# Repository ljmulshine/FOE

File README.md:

# FOE
A collection of embedded design projects carried out in the course, the Frustration of Electronics (FOE), a supervised reading and research course I took during the Spring of my sophomore year. These projects have been added to github after completion of the course to showcase my work. 

## Adjustable Power Supply

This project was the first of three embedded design projects I helped lead in ES91r, the Frustration of Electronics. I worked with two others to design a power supply device, originally intended for use by students in Harvard’s introductory electrical engineering course to power their circuits without the need for a benchtop power supply. I lead my team through the brunt of each major design phase, keeping us on track despite simultaneously pipelining other design projects, short turnarounds between project deadlines, and scheduling difficulties among my teammates. After multiple design iterations, we achieved a fully functional, battery powered, adjustable power supply with overvoltage and overcurrent protection, a dynamic range of 1.5V-10V, and the capacity to source or sink current upwards of 500mA. I am currently iterating upon this preliminary design in order to improve upon the device’s absolute maximum ratings and ergonomics. 

## Instrumentation Device

In the second of three embedded circuit design projects for the course, ES91r, I worked with three others to design a high-precision instrumentation device to interface with a load-cell. Precision was a critical consideration throughout the process; consequently, important design considerations were made to ensure signal integrity: utilizing differential signals and an instrumentation amplifier to combat noise, designing an anti-aliasing filter with appropriate pass and stopband frequencies, ensuring a sufficiently high analog-to-digital conversion rate to allow capture of high-speed events, and making layout design decisions that reduced the effect of digital transients and EMI on the analog signal during its travel to the digital realm. We were able to design hardware to allow us to process our signal digitally and save it to a microSD card; however, we were unable to implement the necessary code for this attribute due to time constraints at the end of the semester. In particular, I left this project with a strong understanding of analog-to-digital conversion, and high-precision analog circuit design. 

## Wireless Charging Station

My team and I designed a Wireless Charging Station meant to interface directly with a small remote-control car. While we were unable to produce a physical prototype, iterating completely through an intense design process - creating our own project specifications, conducting research on wireless power transfer, designing the final circuit and PCB, etc. - on a tight time schedule, not only increased my knowledge of power systems, but also proved to be an excellent project experience, pushing me to make intelligent design decisions under pressure.

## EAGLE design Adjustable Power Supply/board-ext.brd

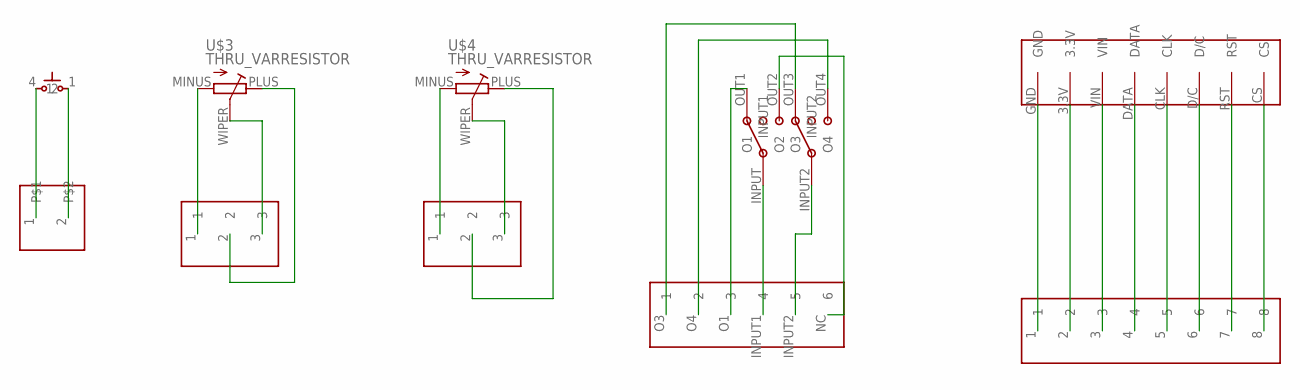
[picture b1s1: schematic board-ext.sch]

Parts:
U$1: 1X02
U$2: BUTTON_THRU; PUSHBTN
U$3, U$4: THRU_VARRESISTOR; POT
U$5, U$6: 1X03
U$7: SWITCH_THRU; DPDT
U$8: 1X06; SWITCHHEAD
U$9: OLED_THRU
U$10: 1X08

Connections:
unnamed: U$1.1, U$2.4 (2)
unnamed: U$1.2, U$2.1
unnamed: U$4.PLUS, U$6.2
unnamed: U$4.MINUS, U$6.1
unnamed: U$4.WIPER, U$6.3
unnamed: U$3.WIPER, U$5.3
unnamed: U$3.PLUS, U$5.2
unnamed: U$3.MINUS, U$5.1
unnamed: U$7.INPUT (INPUT1), U$8.INPUT1 (4)
unnamed: U$7.INPUT2, U$8.INPUT2 (5)
unnamed: U$7.OUT2 (O2), U$8.NC (6)
unnamed: U$7.OUT1 (O1), U$8.O1 (3)
unnamed: U$7.OUT3 (O3), U$8.O3 (1)
unnamed: U$7.OUT4 (O4), U$8.O4 (2)
unnamed: U$9.GND, U$10.1
unnamed: U$9.3.3V, U$10.2
unnamed: U$9.VIN, U$10.3
unnamed: U$9.DATA, U$10.4
unnamed: U$9.CLK, U$10.5
unnamed: U$9.D/C, U$10.6
unnamed: U$9.RST, U$10.7
unnamed: U$9.CS, U$10.8

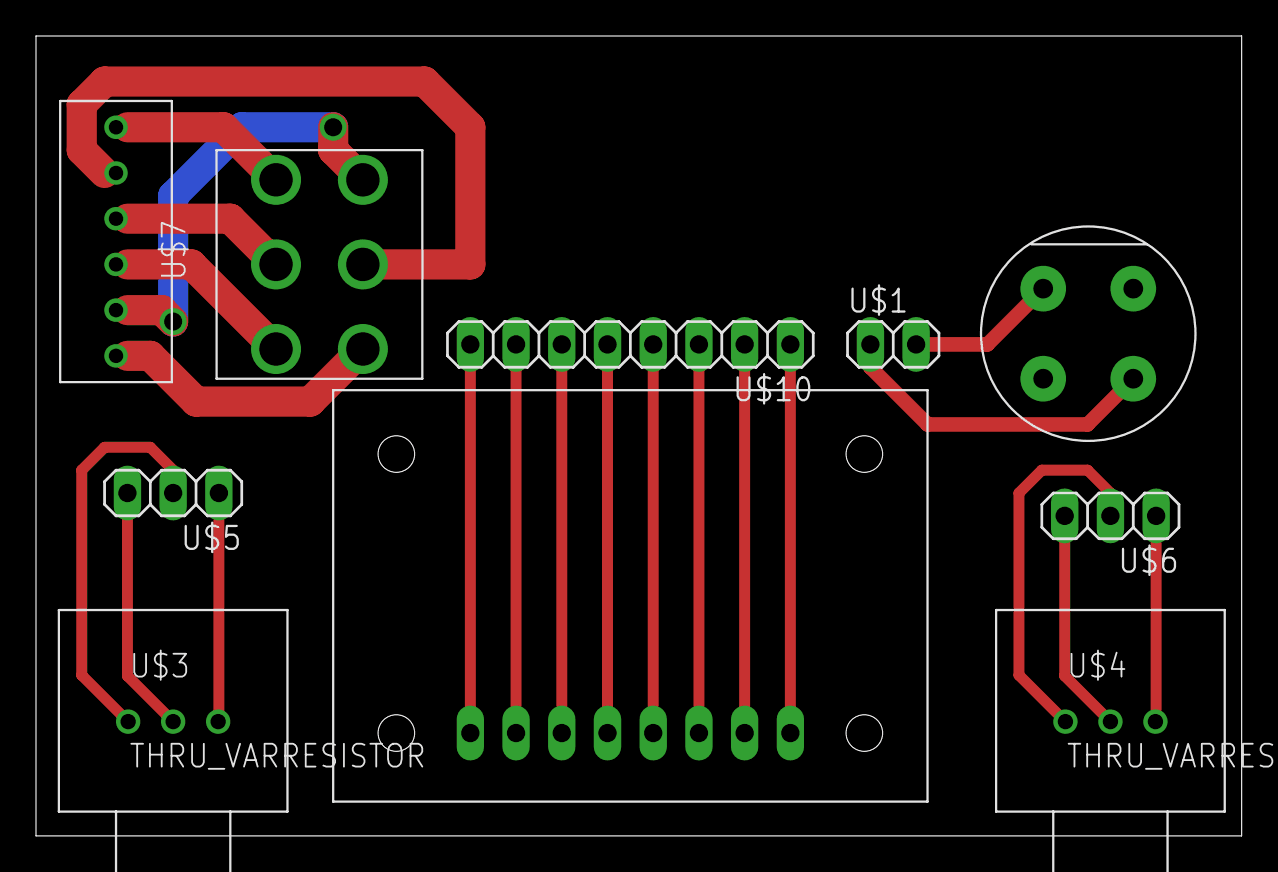
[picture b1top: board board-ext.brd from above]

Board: 2 copper layers, 67.0 x 44.4 mm, 10 parts (0 on the bottom side), 22 nets.

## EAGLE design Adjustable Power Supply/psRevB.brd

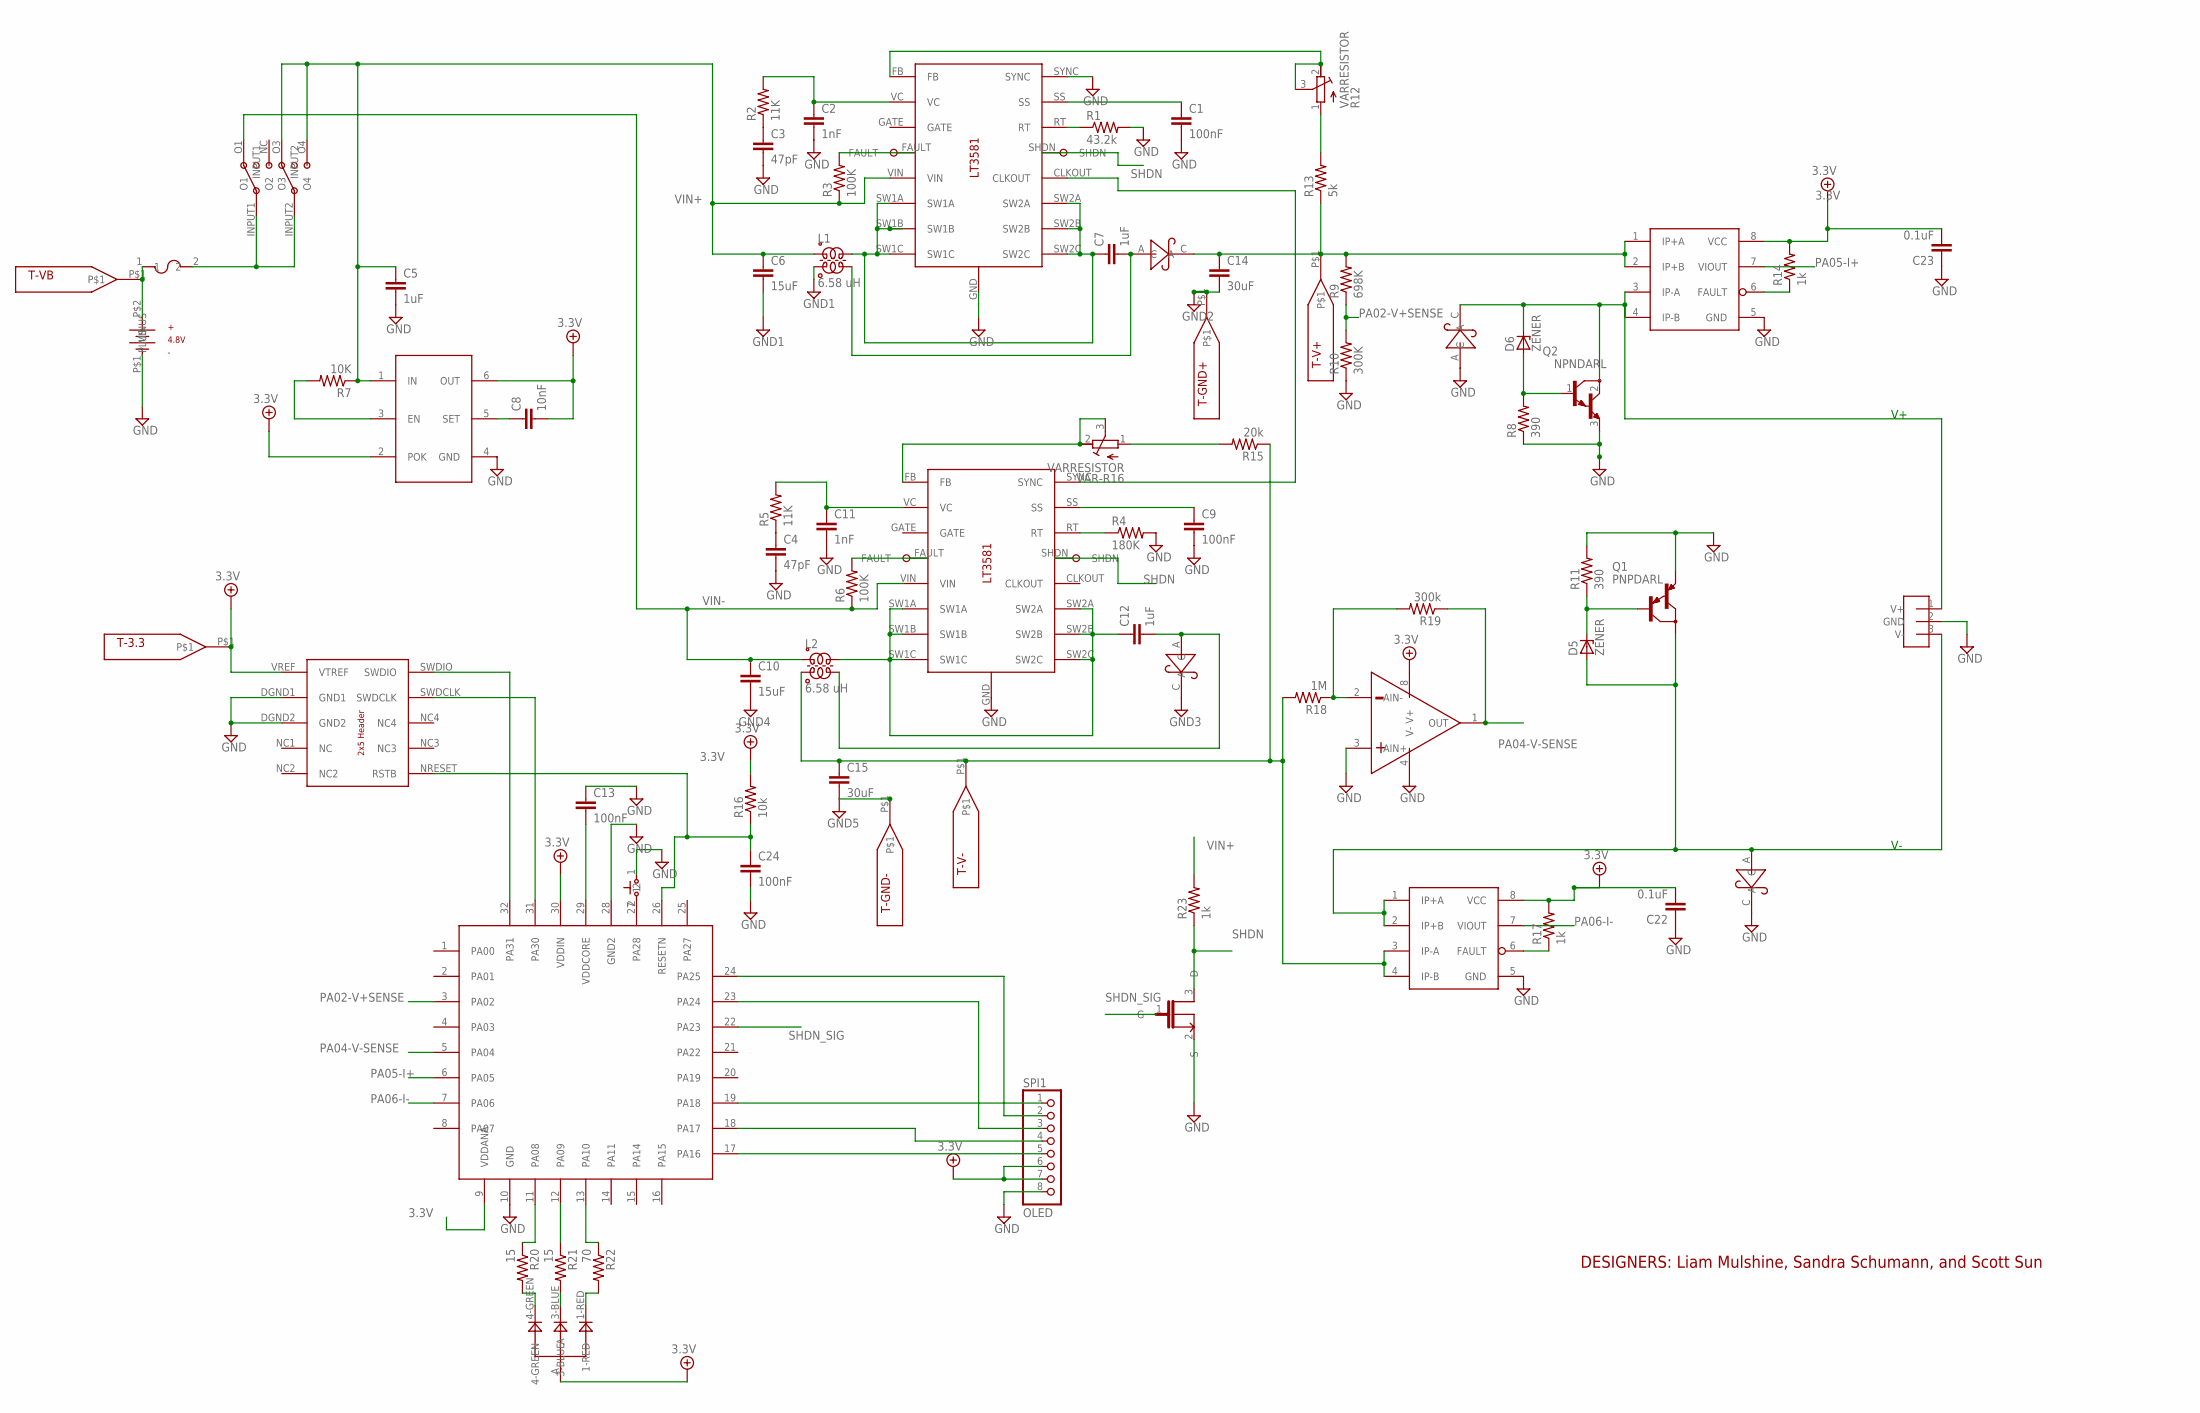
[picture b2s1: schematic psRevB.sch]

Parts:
BT1: BATTERY; POWERHEAD
C1: 100nF; C0603K
C2: 1nF; C0603K
C3: 47pF; C0603K
C4: 47pF; C0805
C5, C7, C12: 1uF; C0805
C6, C10: 15uF; C0805
C8: 10nF; C0805
C9, C13, C24: 100nF; C0805
C11: 1nF; C0805
C14, C15: 30uF; C1206K
C22, C23: 0.1uF; C0805
D1, D2, D3, D4: SCHTKYDIODE
D5, D6: ZENER
DBG1: DEBUGHEAD
F1: FUSE
L1: 6.58 uH; COUPLED_INDUCTOR@1
L2: 6.58 uH; COUPLED_INDUCTOR
Q1: PNPDARL; DPAKTO252
Q2: NPNDARL; DPAKTO252
R1: 43.2k; R0603
R2, R5: 11K; R0603
R3, R6: 100K; R0603
R4: 180K; R0603
R7: 10K; R0603
R8, R11: 390; R0603
R9: 698K; R0603
R10: 300K; R0603
R12: VARRESISTOR; 1X03
R13: 5k; R0603
R14, R17, R23: 1k; R0603
R15: 20k; R0603
R16: 10k; R0603
R18: 1M; R0603
R19: 300k; R0603
R20, R21: 15; R0603
R22: 70; R0603
S1: DPDT; SWITCHHEAD
S2: PUSHBTN; 1X02
SPI1: OLED; 1X08
T-3.3: TEST_POINT
T-GND+: TEST_POINT
T-GND-: TEST_POINT
T-V+: TEST_POINT
T-V-: TEST_POINT
T-VB: TEST_POINT
U1, U7: LT3581
U2: SAMD21E; TQFP32-08
U3: AS1363; SOT23-6
U4: VOUT; 1X03
U5, U6: ACS711; SOIC8
U8: RGBLED
U9: LMC6482; SOIC8
U$1: NMOS; SOT23-3
VAR-R16: VARRESISTOR; 1X03

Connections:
3.3V: C8.2, C22.2, C23.2, DBG1.VREF (VTREF), R14.2, R16.2, R17.2, SPI1.6 (VIN1), SPI1.7 (VIN2), T-3.3.P$1, U2.9 (VDDANA), U2.30 (VDDIN), U3.2 (POK), U3.6 (OUT), U5.8 (VCC), U6.8 (VCC), U8.A, U9.8 (V+)
GND: BT1.P$1 (MINUS), C1.2, C2.2, C3.2, C4.2, C5.2, C6.2, C9.2, C10.2, C11.2, C13.1, C14.2, C15.2, C22.1, C23.1, C24.2, D1.C, D2.C, D3.A, DBG1.DGND1 (GND1), DBG1.DGND2 (GND2), L1.L2A (2), Q1.3 (E), Q2.3 (E), R1.2, R4.2, R8.1, R10.1, R11.2, S2.1, SPI1.8 (GND), T-GND+.P$1, T-GND-.P$1, U1.GND, U1.SYNC, U2.10 (GND), U2.28 (GND2), U3.4 (GND), U4.2 (GND), U5.5 (GND), U6.5 (GND), U7.GND, U9.3 (AIN+), U9.4 (V-), U$1.2 (S)
unnamed: R1.1, U1.RT
unnamed: C1.1, U1.SS
unnamed: C3.1, R2.1
unnamed: C2.1, R2.2, U1.VC
unnamed: R4.1, U7.RT
unnamed: C9.1, U7.SS
unnamed: C4.1, R5.1
unnamed: C11.1, R5.2, U7.VC
unnamed: S2.2, U2.27 (PA28)
unnamed: D3.C, D6.C, Q2.2 (C), U4.1 (V+), U5.3 (IP-A), U5.4 (IP-B)
unnamed: C12.2, D1.A, L2.L2B (4)
unnamed: R17.1, U6.6 (FAULT)
unnamed: C8.1, U3.5 (SET)
unnamed: U7.FB, VAR-R16.2 (PLUS), VAR-R16.3 (WIPER)
unnamed: R12.2 (PLUS), R12.3 (WIPER), U1.FB
unnamed: R7.2, U3.3 (EN)
unnamed: C24.1, DBG1.NRESET (RSTB), R16.1, U2.26 (RESETN)
unnamed: D6.A, Q2.1 (B), R8.2
unnamed: BT1.P$2 (PLUS), F1.1, T-VB.P$1
unnamed: C7.1, L1.L1B (3), U1.SW1A, U1.SW1B, U1.SW1C, U1.SW2A, U1.SW2B, U1.SW2C
unnamed: C12.1, L2.L1B (3), U7.SW1A, U7.SW1B, U7.SW1C, U7.SW2A, U7.SW2B, U7.SW2C
unnamed: R15.2, VAR-R16.1 (MINUS)
unnamed: C7.2, D4.A, L1.L2B (4)
unnamed: D5.C, Q1.1 (B), R11.1
unnamed: C15.1, L2.L2A (2), R15.1, R18.2, T-V-.P$1, U6.3 (IP-A), U6.4 (IP-B)
unnamed: C14.1, D4.C, R9.2, R13.1, T-V+.P$1, U5.1 (IP+A), U5.2 (IP+B)
unnamed: R12.1 (MINUS), R13.2
unnamed: R18.1, R19.2, U9.2 (AIN-)
unnamed: R14.1, U5.6 (FAULT)
unnamed: R20.2, U8.4-GREEN
unnamed: R21.2, U8.3-BLUE
unnamed: R22.2, U8.1-RED
unnamed: D2.A, D5.A, Q1.2 (C), U4.3 (V-), U6.1 (IP+A), U6.2 (IP+B)
unnamed: R20.1, U2.11 (PA08)
unnamed: R21.1, U2.12 (PA09)
unnamed: R22.1, U2.13 (PA10)
unnamed: C13.2, U2.29 (VDDCORE)
unnamed: DBG1.SWDIO, U2.32 (PA31)
unnamed: DBG1.SWDCLK, U2.31 (PA30)
unnamed: SPI1.1 (CS), U2.19 (PA18)
unnamed: SPI1.2 (RST), U2.24 (PA25)
unnamed: SPI1.3 (D/C), U2.23 (PA24)
unnamed: SPI1.5 (DATA), U2.17 (PA16)
unnamed: SPI1.4 (CLK), U2.18 (PA17)
unnamed: F1.2, S1.INPUT1, S1.INPUT2
PA02-V+SENSE: R9.1, R10.2, U2.3 (PA02)
PA04-V-SENSE: R19.1, U2.5 (PA04), U9.1 (OUT)
PA05-I+: U2.6 (PA05), U5.7 (VIOUT)
PA06-I-: U2.7 (PA06), U6.7 (VIOUT)
PA11-FAULT1: R3.2, U1.FAULT
PA19-FAULT2: R6.2, U7.FAULT
SHDN: R23.1, U1.SHDN, U7.SHDN, U$1.3 (D)
SHDN_SIG: U2.22 (PA23), U$1.1 (G)
SYNC: U1.CLKOUT, U7.SYNC
VIN+: C5.1, C6.1, L1.L1A (1), R3.1, R7.1, R23.2, S1.O3, S1.O4, U1.VIN, U3.1 (IN)
VIN-: C10.1, L2.L1A (1), R6.1, S1.O1, U7.VIN

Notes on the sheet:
DESIGNERS: Liam Mulshine, Sandra Schumann, and Scott Sun

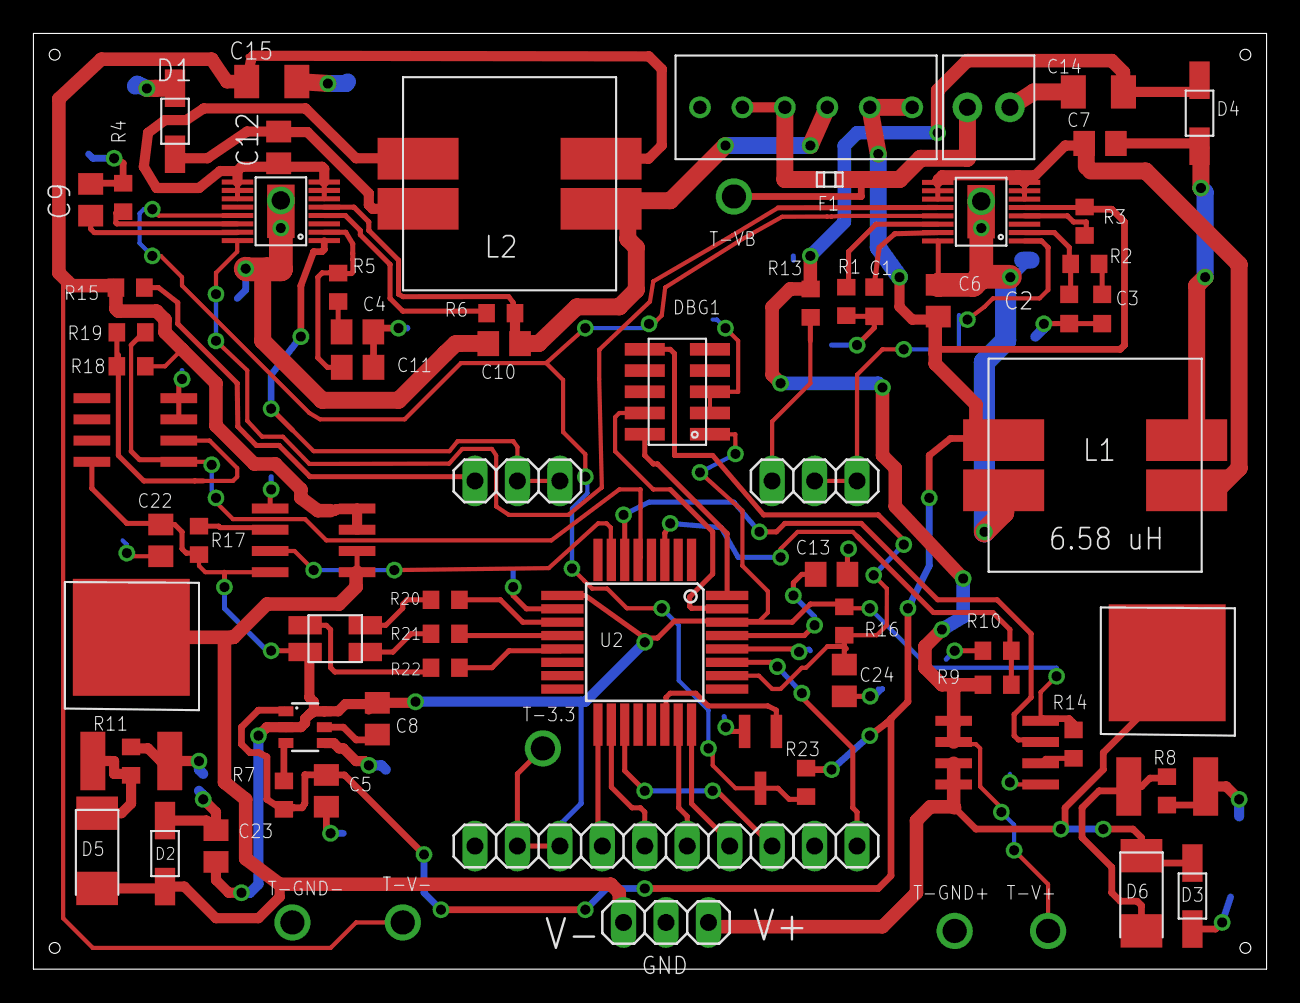
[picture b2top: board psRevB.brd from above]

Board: 2 copper layers, 73.8 x 56.0 mm, 74 parts (0 on the bottom side), 58 nets.

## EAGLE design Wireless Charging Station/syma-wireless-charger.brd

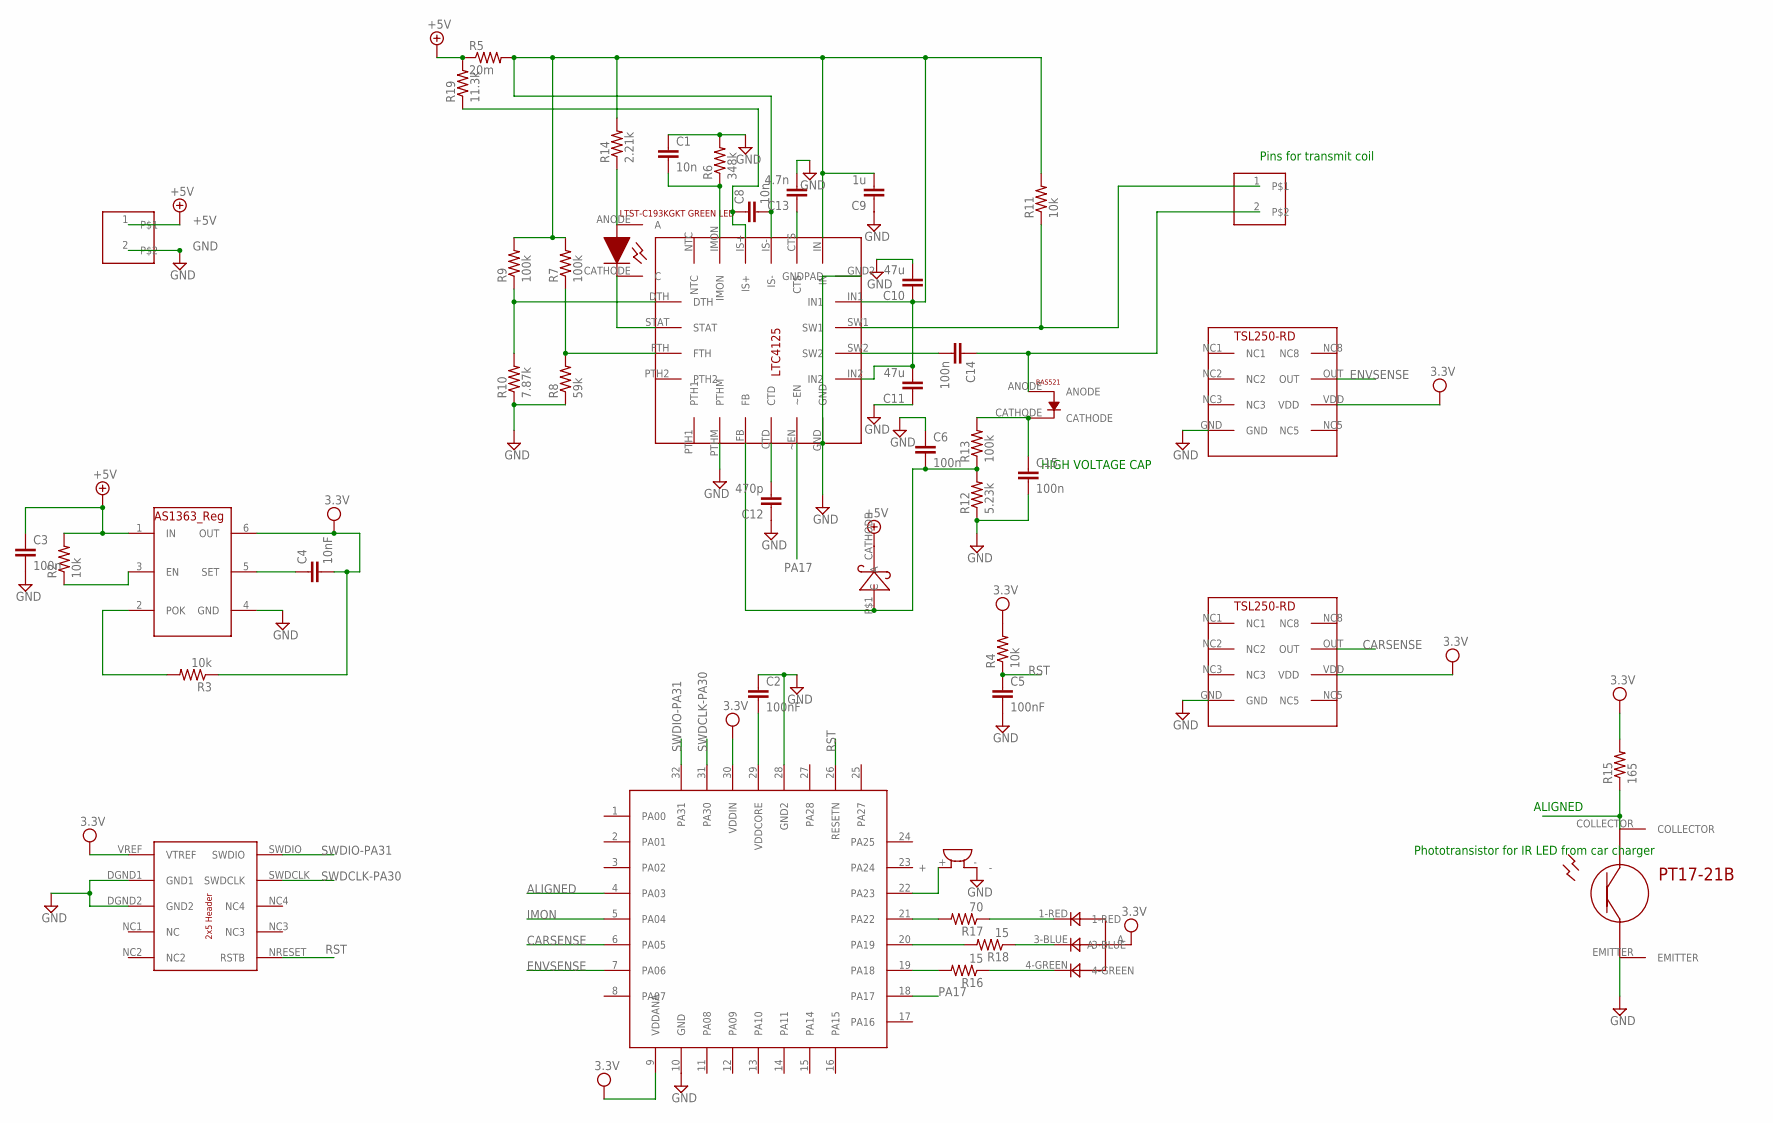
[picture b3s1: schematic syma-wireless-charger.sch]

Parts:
C1, C8: 10n; C0805
C2, C5: 100nF; C0805K
C3: 100n; C0805K
C4: 10nF; C0805K
C6: 100n; C0805
C9: 1u; C0805
C10, C11: 47u; C0805
C12: 470p; C0805
C13: 4.7n; C0805
C14: 100n; C1206
C15: 100n; C0603
DBG1: DEBUGHEAD
R2, R3, R4, R11: 10k; R0805
R5: 20m; R0805
R6: 348k; R0805
R7, R9, R13: 100k; R0805
R8: 59k; R0805
R10: 7.87k; R0805
R12: 5.23k; R0805
R14: 2.21k; R0805
R15: 165; R0805
R16, R18: 15; R0805
R17: 70; R0805
R19: 11.3k; R0805
U1: SAMD21E; TQFP32-08
U2: 3.3V_AS1363; SOT23-6
U$1: LTC4125; LTC1945-QFN
U$2: BAS521; BAS521-V-DIODE
U$3, U$11: 1X02
U$4: RGBLED
U$5: BUZZER
U$6, U$7: TSL250-RD
U$8: SCHTKYDIODE-523; SOD-523
U$9: LTST-C193KGKT_GREEN-LED
U$10: PT17-21B_PHOTOTRANSISTOR

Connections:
+5V: C3.1, R2.2, R5.1, R19.2, U2.1 (IN), U$3.1, U$8.CATHODE (C)
ALIGNED: R15.1, U1.4 (PA03), U$10.COLLECTOR
CARSENSE: U1.6 (PA05), U$6.OUT
ENVSENSE: U1.7 (PA06), U$7.OUT
GND: C1.1, C2.1, C3.2, C5.2, C6.1, C9.1, C10.2, C11.1, C12.1, C13.2, C15.2, DBG1.DGND1 (GND1), DBG1.DGND2 (GND2), R6.2, R8.1, R10.1, R12.1, U1.10 (GND), U1.28 (GND2), U2.4 (GND), U$1.GND, U$1.GND2 (GNDPAD), U$1.PTHM, U$3.2, U$5.-, U$6.GND, U$7.GND, U$10.EMITTER
IMON: C1.2, R6.1, U1.5 (PA04), U$1.IMON
unnamed: C2.2, U1.29 (VDDCORE)
unnamed: R3.2, U2.2 (POK)
unnamed: R2.1, U2.3 (EN)
unnamed: R9.1, R10.2, U$1.DTH
unnamed: C4.1, U2.5 (SET)
unnamed: R7.1, R8.2, U$1.FTH
unnamed: R11.1, U$1.SW1, U$11.1
unnamed: C6.2, R12.2, R13.1, U$1.FB, U$8.P$1 (A)
unnamed: C15.1, R13.2, U$2.CATHODE
unnamed: R14.1, U$9.ANODE (A)
unnamed: C14.1, U$2.ANODE, U$11.2
unnamed: R17.2, U1.21 (PA22)
unnamed: R18.2, U1.20 (PA19)
unnamed: R16.2, U1.19 (PA18)
unnamed: R16.1, U$4.4-GREEN
unnamed: R18.1, U$4.3-BLUE
unnamed: R17.1, U$4.1-RED
unnamed: U1.22 (PA23), U$5.+
unnamed: C8.2, C9.2, C10.1, C11.2, R5.2, R7.2, R9.2, R11.2, R14.2, U$1.IN, U$1.IN1, U$1.IN2, U$1.IS-
unnamed: C8.1, R19.1, U$1.IS+
unnamed: C14.2, U$1.SW2
unnamed: U$1.STAT, U$9.CATHODE (C)
unnamed: C12.2, U$1.CTD
unnamed: C13.1, U$1.CTS
PA17: U1.18 (PA17), U$1.~EN
RST: C5.1, DBG1.NRESET (RSTB), R4.1, U1.26 (RESETN)
SWDCLK-PA30: DBG1.SWDCLK, U1.31 (PA30)
SWDIO-PA31: DBG1.SWDIO, U1.32 (PA31)
VDD: C4.2, DBG1.VREF (VTREF), R3.1, R4.2, R15.2, U1.9 (VDDANA), U1.30 (VDDIN), U2.6 (OUT), U$4.A, U$6.VDD, U$7.VDD

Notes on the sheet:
Phototransistor for IR LED from car charger
Pins for transmit coil
HIGH VOLTAGE CAP
ALIGNED

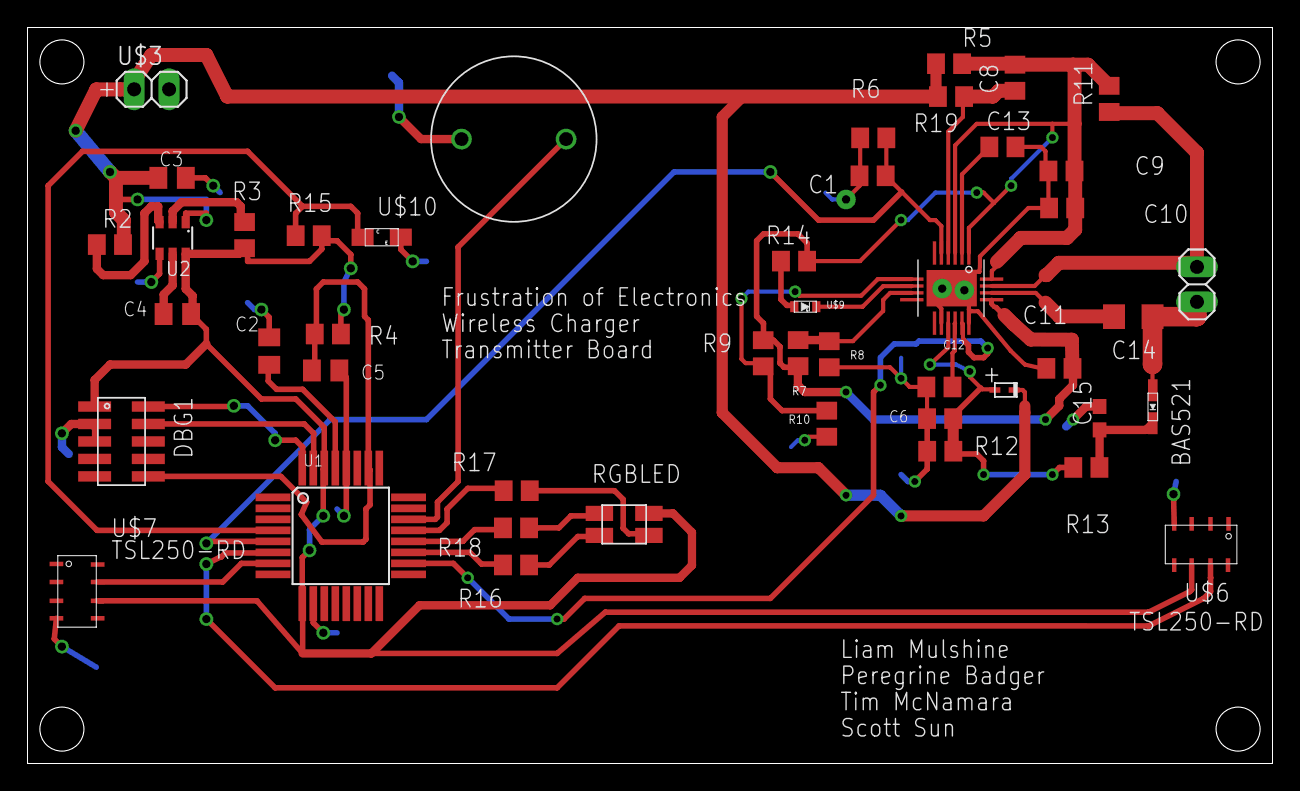
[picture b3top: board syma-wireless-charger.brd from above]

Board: 2 copper layers, 90.5 x 53.5 mm, 46 parts (0 on the bottom side), 35 nets.

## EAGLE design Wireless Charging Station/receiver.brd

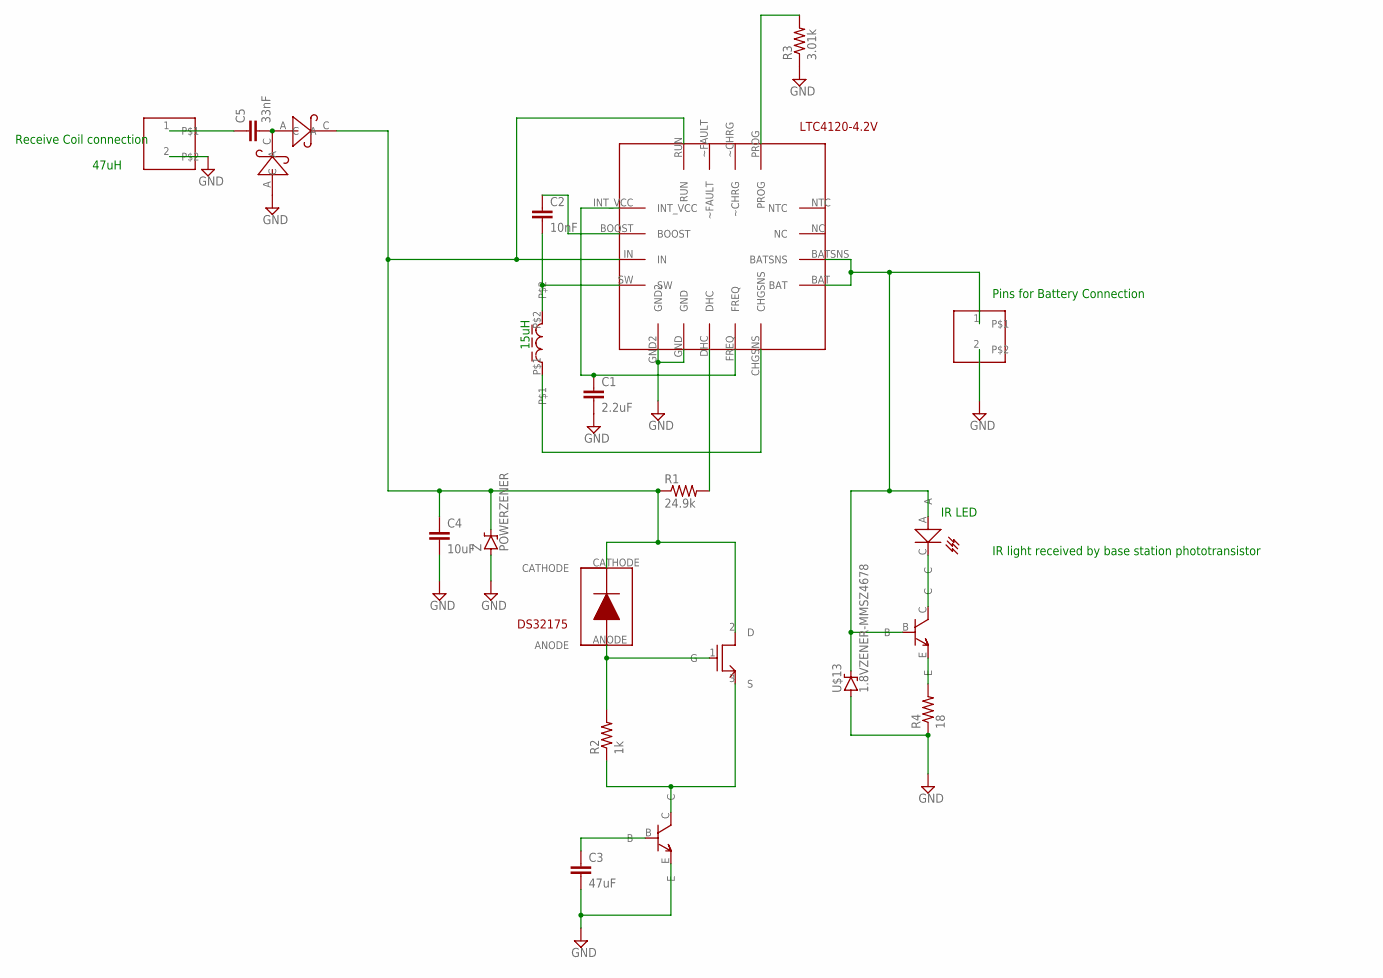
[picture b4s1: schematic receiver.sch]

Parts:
C1: 2.2uF; C0805K
C2: 10nF; C0805K
C3: 47uF; C0805K
C4: 10uF; C0805K
C5: 33nF; C0805K
PS, PS2: SCHTKYPOWER; POWERDI123
R1: 24.9k; R0805
R2: 1k; R0805
R3: 3.01k; R0805
R4: 18; R0805
U$1: LTC4120-4.2V
U$2, U$10: 1X02
U$3: 15UH-INDUCTOR
U$4: BAS521; BAS521-V-DIODE
U$5: M1-RSD140P06; DPAKTO252
U$6, U$14: NPN-MMBT3904; SOT23
U$11: IRLED
U$13: 1.8VZENER-MMSZ4678; SOD-123
Z: POWERZENER; POWERDI123

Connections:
GND: C1.2, C3.2, C4.2, PS2.A, R3.1, R4.1, U$1.GND, U$1.GND2, U$2.2, U$6.E, U$10.2, U$13.A, Z.A
unnamed: C1.1, U$1.FREQ, U$1.INT_VCC
unnamed: U$1.CHGSNS, U$3.P$1
unnamed: C4.1, PS.C, R1.1, U$1.IN, U$1.RUN, U$4.CATHODE, U$5.2 (D), Z.C
unnamed: C2.1, U$1.BOOST
unnamed: C2.2, U$1.SW, U$3.P$2
unnamed: R1.2, U$1.DHC
unnamed: R2.2, U$4.ANODE, U$5.1 (G)
unnamed: R2.1, U$5.3 (S), U$6.C
unnamed: C5.1, U$2.1
unnamed: C5.2, PS.A, PS2.C
unnamed: C3.1, U$6.B
unnamed: R3.2, U$1.PROG
unnamed: U$1.BAT, U$1.BATSNS, U$10.1, U$11.A, U$13.C, U$14.B
unnamed: R4.2, U$14.E
unnamed: U$11.C, U$14.C

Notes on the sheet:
15uH
Pins for Battery Connection
IR LED
IR light received by base station phototransistor
Receive Coil connection
47uH

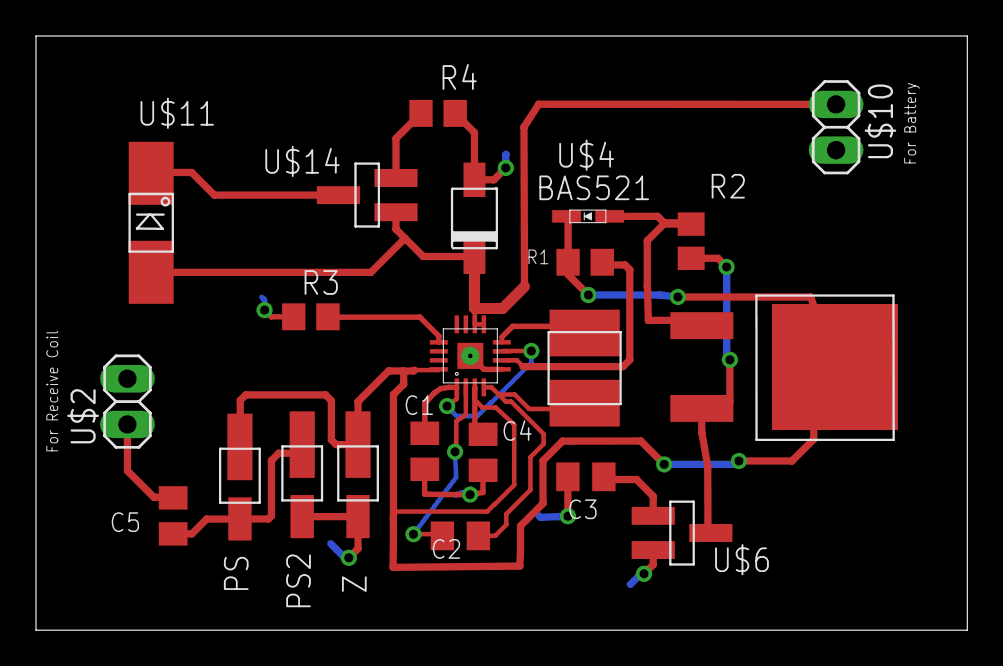
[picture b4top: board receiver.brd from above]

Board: 2 copper layers, 51.7 x 33.0 mm, 22 parts (0 on the bottom side), 16 nets.

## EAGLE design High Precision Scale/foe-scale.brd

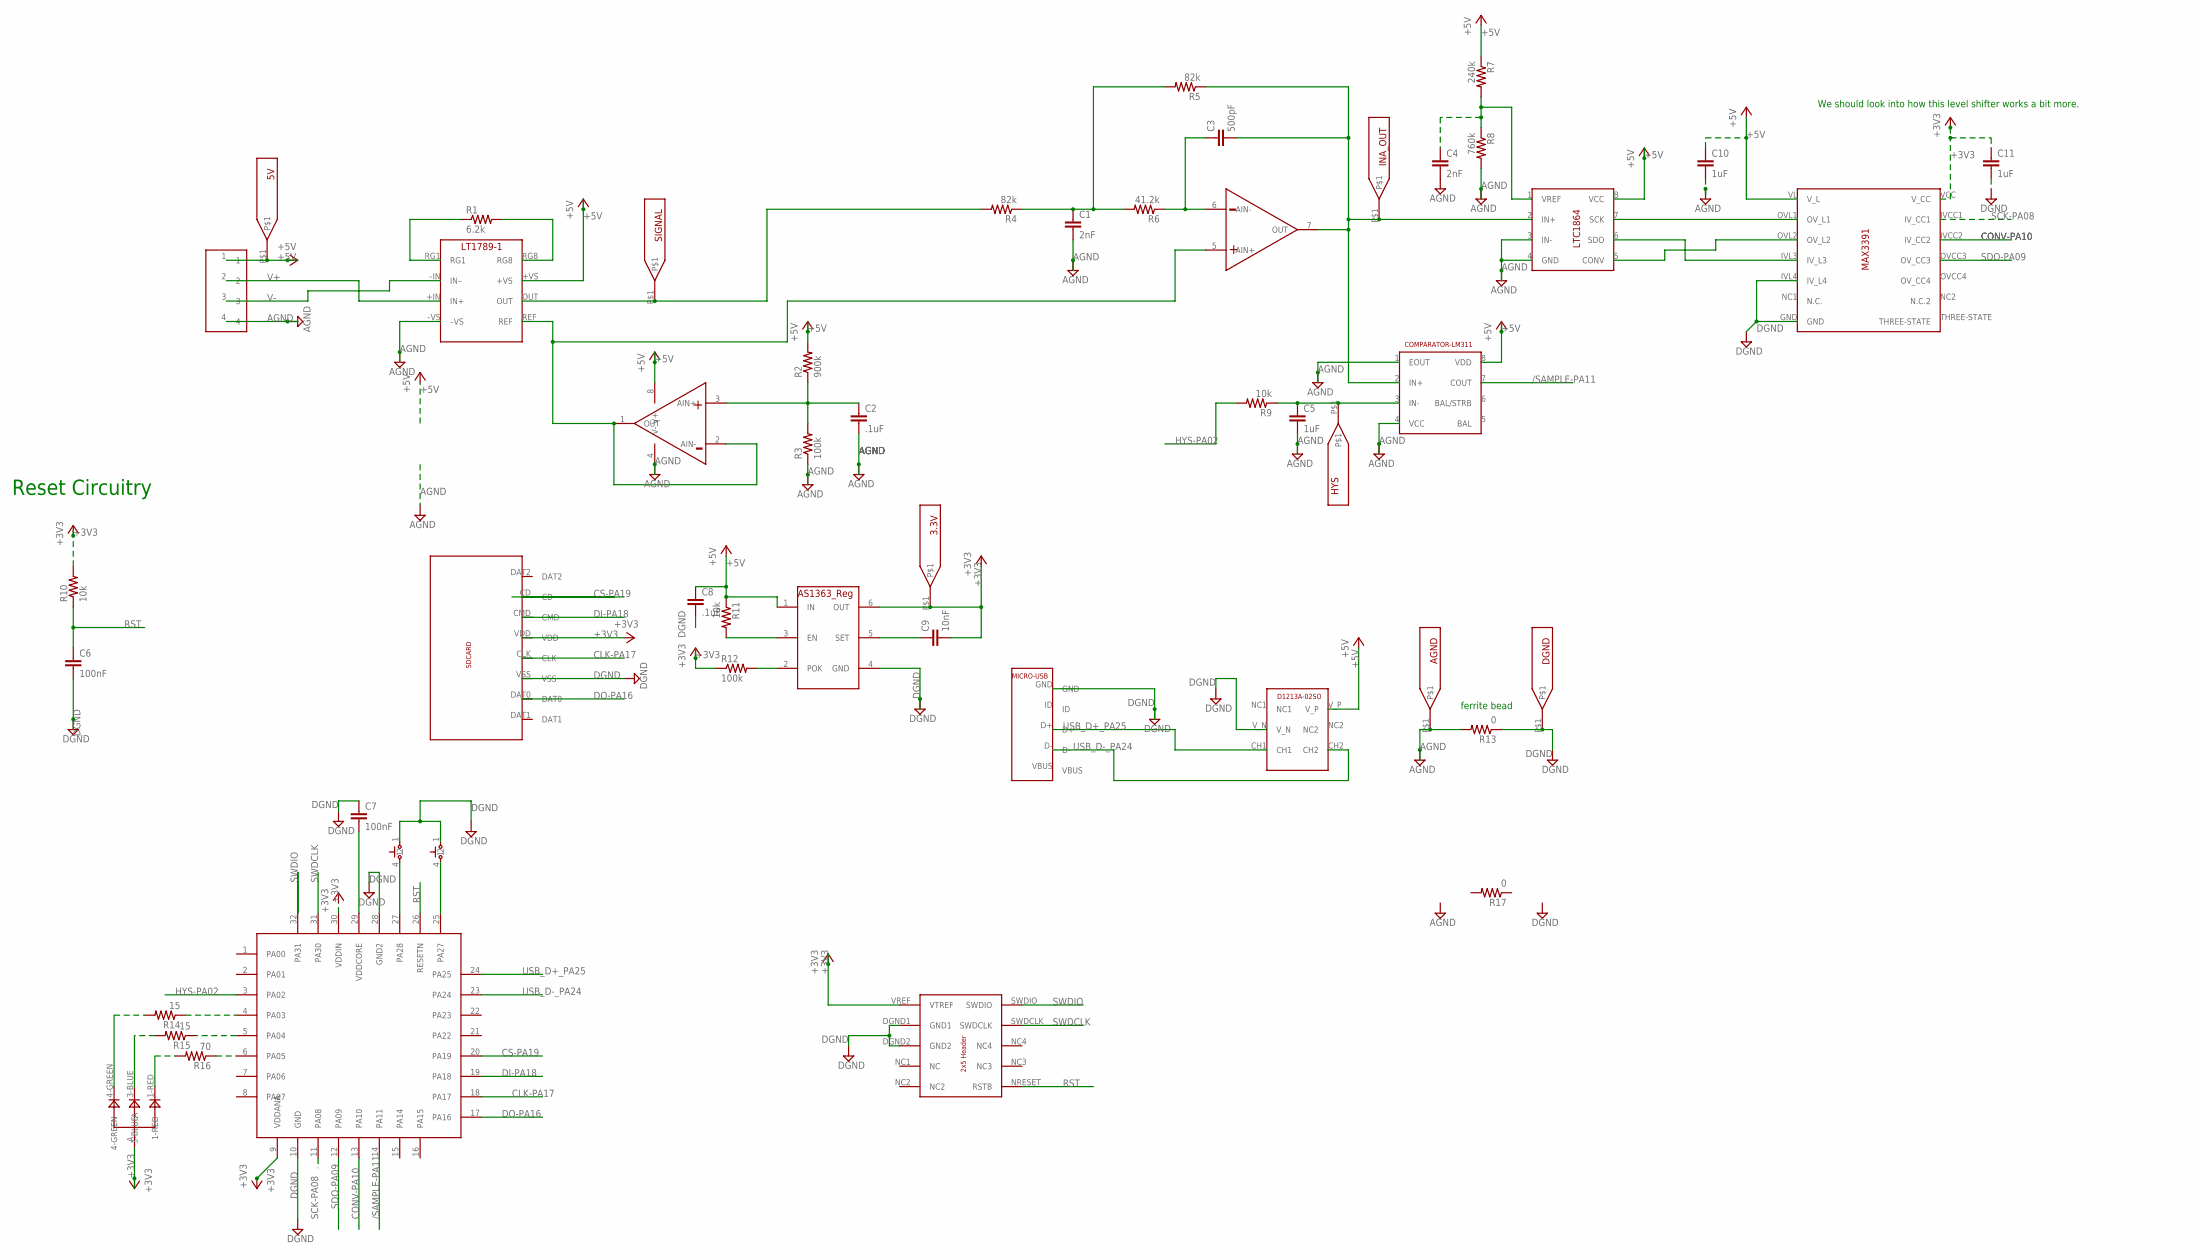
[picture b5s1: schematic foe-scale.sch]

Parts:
3.3V, 5V: TEST_POINT
AGND: TEST_POINT
AS1363: 3.3V_AS1363; SOT23-6
C1, C4: 2nF; C0805K
C2, C8: .1uF; C0805K
C3: 500pF; C0805K
C5, C10, C11: 1uF; C0805K
C6, C7: 100nF; C0805K
C9: 10nF; C0805K
D1: D1213A-DIODE-ARRAY; SOT26-DIODE-ARRAY
DBG1: DEBUGHEAD
DGND: TEST_POINT
HYS: TEST_POINT
INA_OUT: TEST_POINT
R1: 6.2k; R0805
R2: 900k; R0805
R3, R12: 100k; R0805
R4, R5: 82k; R0805
R6: 41.2k; R0805
R7: 240k; R0805
R8: 760k; R0805
R9, R10, R11: 10k; R0805
R13, R17: 0; R0805
R14, R15: 15; R0805
R16: 70; R0805
SIGNAL: TEST_POINT
U1: LM311; SOIC8
U2: SAMD21E; TQFP32-08
U$1: 1X04
U$2: LT1789-1-INSTR-AMP; S8-LT1789-1
U$3: LMC6482; SOIC8
U$6: ADC-LTC1864; SOIC8
U$7: LEVEL-SHIFTER; TSSOP-14
U$8: SDCARD_JACK; MICRO_SDCARD
U$10: RGBLED
U$11, U$12: BUTTON_THRU; PUSHBTN
U$13: MICRO-USB-CONNECTOR

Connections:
+3V3: 3.3V.P$1, AS1363.6 (OUT), C9.2, C11.1, DBG1.VREF (VTREF), R10.2, R12.1, U2.9 (VDDANA), U2.30 (VDDIN), U$7.VCC (V_CC), U$8.VDD, U$10.A
+5V: 5V.P$1, AS1363.1 (IN), C8.1, C10.1, D1.V_P, R2.2, R7.1, R11.1, U1.8 (VDD), U$1.1, U$2.+VS, U$3.8 (V+), U$6.8 (VCC), U$7.VL (V_L)
/SAMPLE-PA11: U1.7 (COUT), U2.14 (PA11)
AGND: AGND.P$1, C1.2, C2.2, C4.2, C5.2, C10.2, R3.1, R8.2, R13.2, U1.1 (EOUT), U1.4 (VCC), U$1.4, U$2.–VS, U$3.4 (V-), U$6.3 (IN-), U$6.4 (GND)
CLK-PA17: U2.18 (PA17), U$8.CLK
CONV-PA10: U2.13 (PA10), U$7.IVCC2 (IV_CC2)
CS-PA19: U2.20 (PA19), U$8.CD
DGND: AS1363.4 (GND), C6.2, C7.1, C8.2, C11.2, D1.V_N, DBG1.DGND1 (GND1), DBG1.DGND2 (GND2), DGND.P$1, R13.1, U2.10 (GND), U2.28 (GND2), U$7.GND, U$7.IVL4 (IV_L4), U$8.VSS, U$11.1, U$12.1, U$13.GND
DI-PA18: U2.19 (PA18), U$8.CMD
DO-PA16: U2.17 (PA16), U$8.DAT0
HYS-PA02: R9.2, U2.3 (PA02)
unnamed: R14.1, U2.4 (PA03)
unnamed: U2.27 (PA28), U$12.4 (2)
unnamed: U2.25 (PA27), U$11.4 (2)
unnamed: R15.1, U2.5 (PA04)
unnamed: R1.1, U$2.RG1
unnamed: R1.2, U$2.RG8
unnamed: R4.2, SIGNAL.P$1, U$2.OUT
unnamed: R16.1, U2.6 (PA05)
unnamed: C2.1, R2.1, R3.2, U$3.3 (AIN+)
unnamed: U$2.REF, U$3.1 (OUT), U$3.2 (AIN-), U$3.5 (AIN+)
unnamed: C1.1, R4.1, R5.2, R6.2
unnamed: C3.2, INA_OUT.P$1, R5.1, U1.2 (IN+), U$3.7 (OUT), U$6.2 (IN+)
unnamed: C3.1, R6.1, U$3.6 (AIN-)
unnamed: C4.1, R7.2, R8.1, U$6.1 (VREF)
unnamed: C5.1, HYS.P$1, R9.1, U1.3 (IN-)
unnamed: U$6.7 (SCK), U$7.OVL1 (OV_L1)
unnamed: U$6.5 (CONV), U$7.OVL2 (OV_L2)
unnamed: U$6.6 (SDO), U$7.IVL3 (IV_L3)
unnamed: C7.2, U2.29 (VDDCORE)
unnamed: R14.2, U$10.4-GREEN
unnamed: R15.2, U$10.3-BLUE
unnamed: R16.2, U$10.1-RED
unnamed: AS1363.3 (EN), R11.2
unnamed: AS1363.5 (SET), C9.1
unnamed: AS1363.2 (POK), R12.2
RST: C6.1, DBG1.NRESET (RSTB), R10.1, U2.26 (RESETN)
SCK-PA08: U2.11 (PA08), U$7.IVCC1 (IV_CC1)
SDO-PA09: U2.12 (PA09), U$7.OVCC3 (OV_CC3)
SWDCLK: DBG1.SWDCLK, U2.31 (PA30)
SWDIO: DBG1.SWDIO, U2.32 (PA31)
USB_D+_PA25: D1.CH1, U2.24 (PA25), U$13.D+
USB_D-_PA24: D1.CH2, U2.23 (PA24), U$13.D-
V+: U$1.2, U$2.+IN (IN+)
V-: U$1.3, U$2.–IN (IN–)

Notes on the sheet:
We should look into how this level shifter works a bit more.
Reset Circuitry
ferrite bead

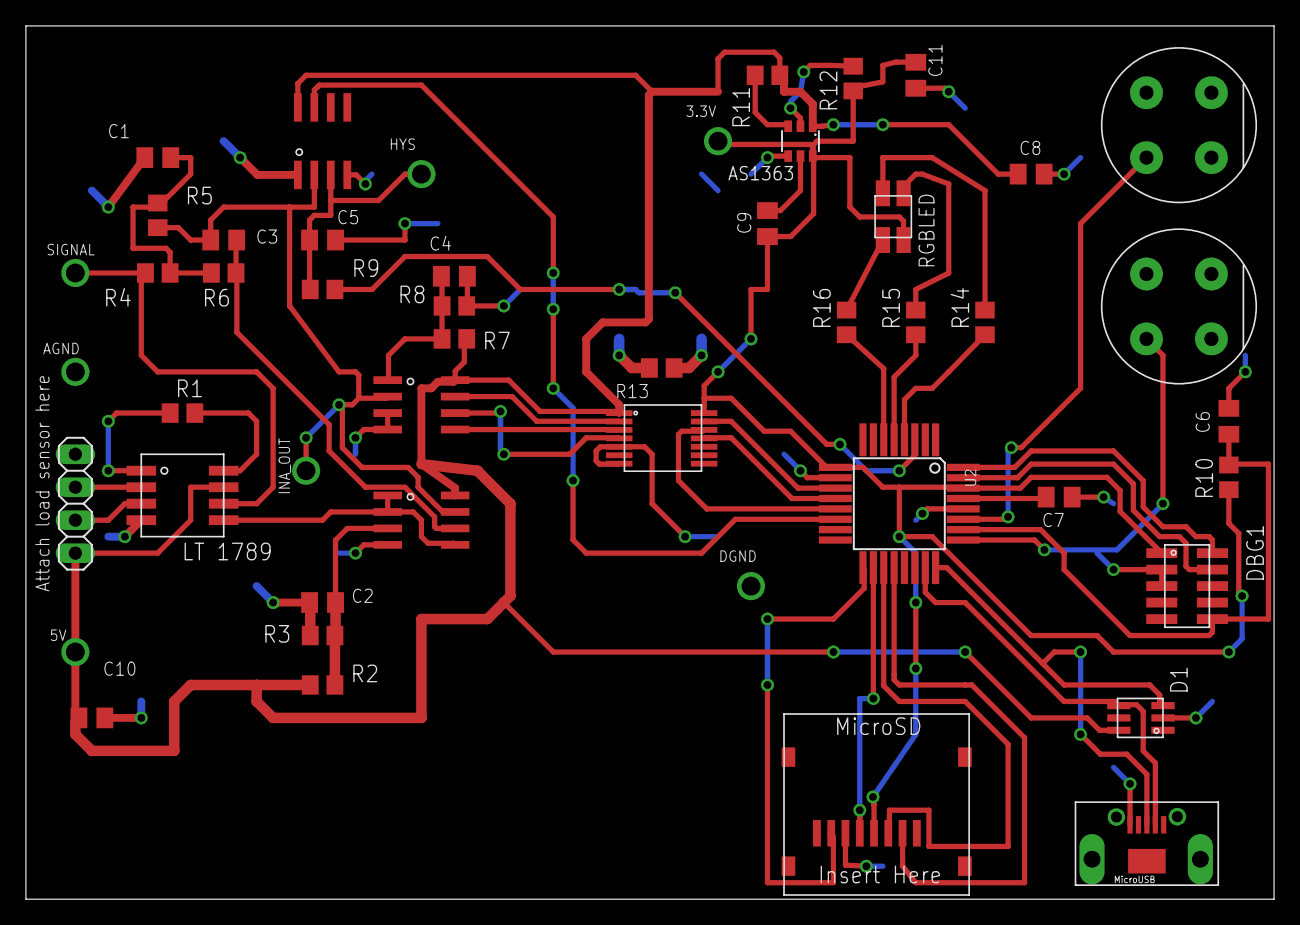
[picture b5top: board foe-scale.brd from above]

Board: 2 copper layers, 96.2 x 67.3 mm, 49 parts (0 on the bottom side), 45 nets.
